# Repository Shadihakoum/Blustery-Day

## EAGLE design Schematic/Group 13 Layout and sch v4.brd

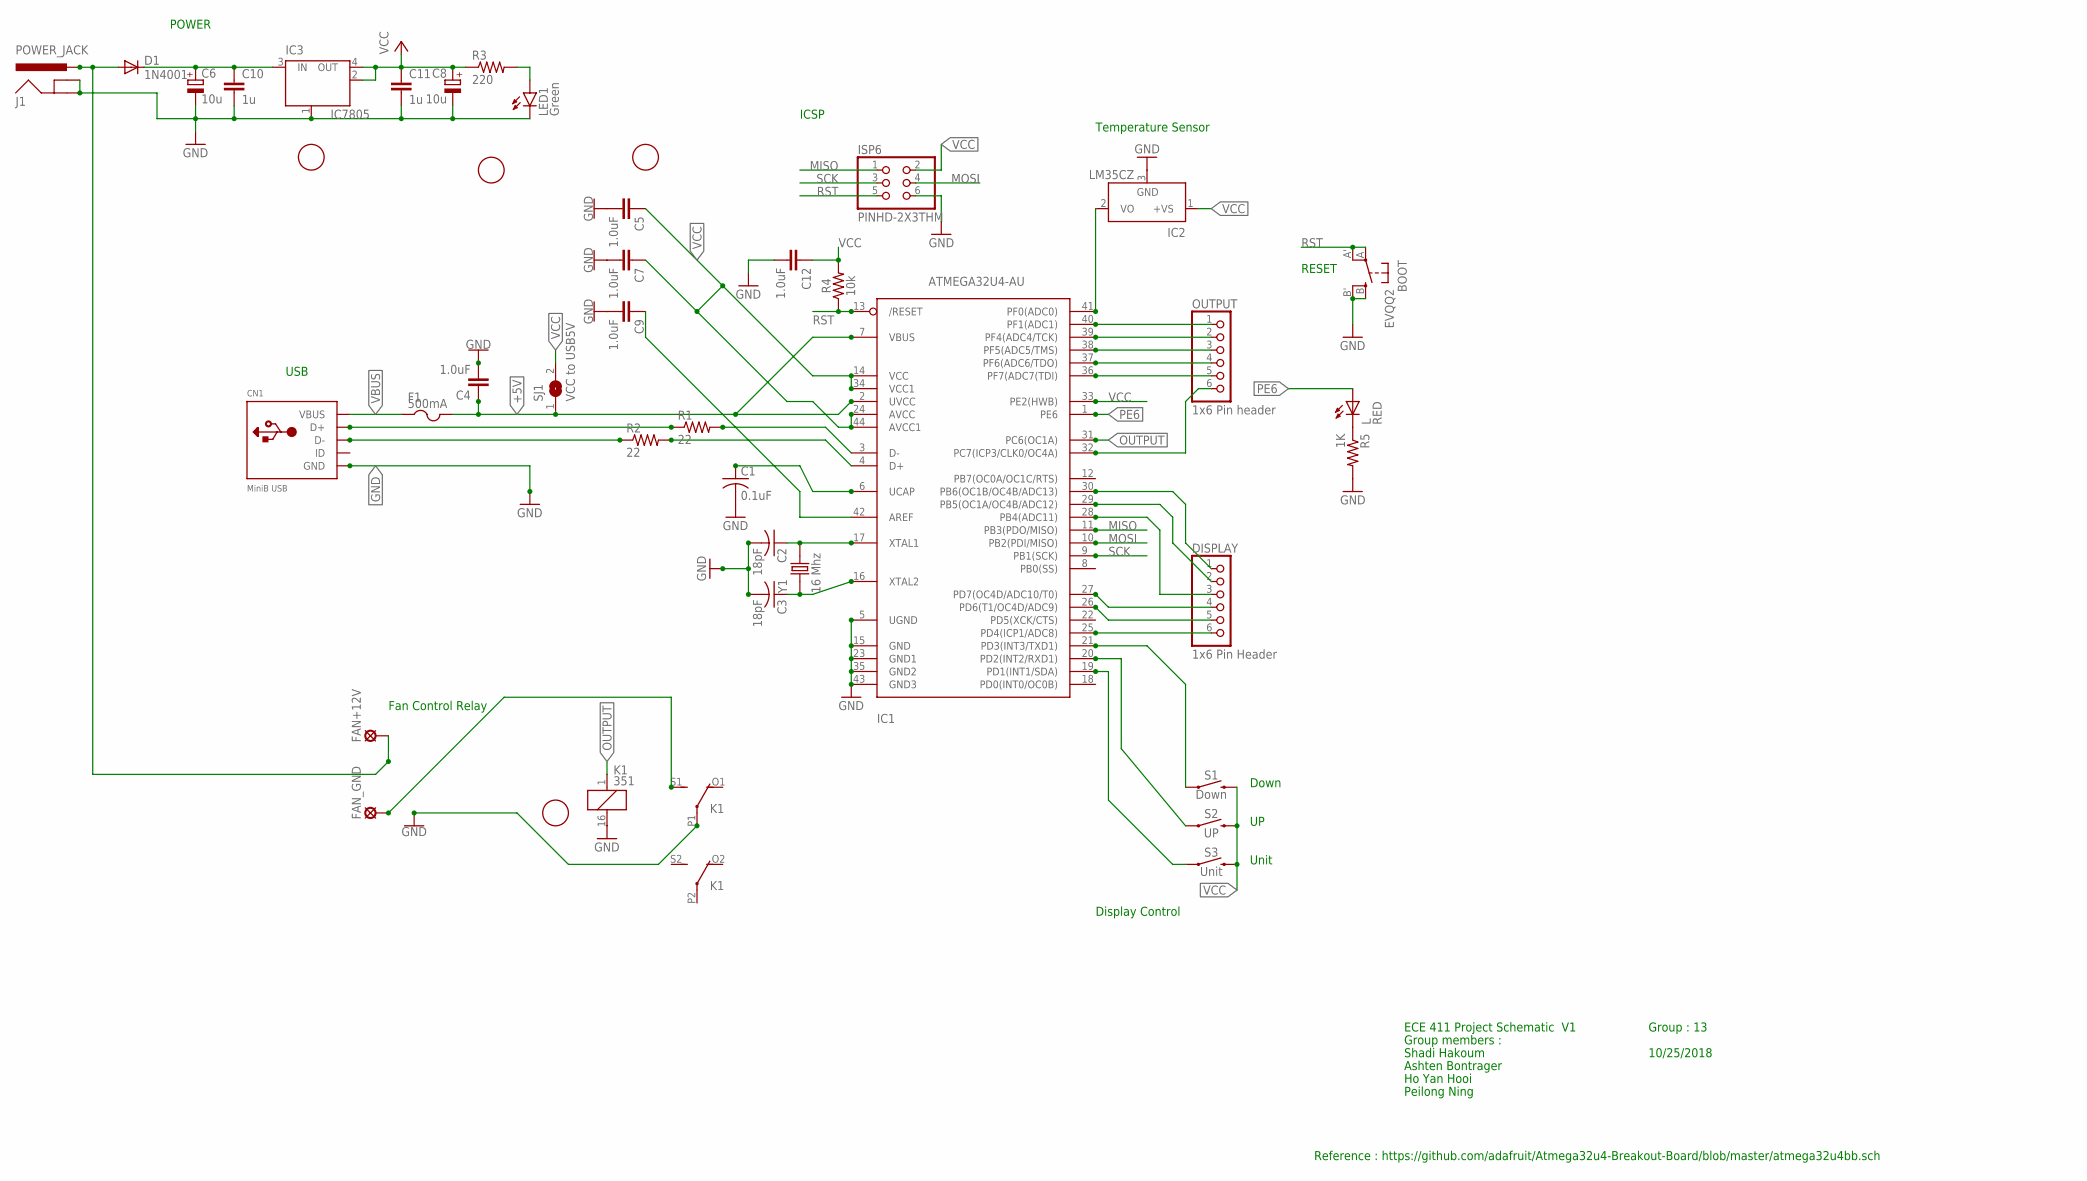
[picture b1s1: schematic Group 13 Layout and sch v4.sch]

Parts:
BOOT: EVQQ2; EVQ-Q2
C1: 0.1uF; C0805K
C2, C3: 18pF; C0805K
C4, C5, C7, C9, C12: 1.0uF; 0603
C6, C8: 10u; PANASONIC_C
C10, C11: 1u; C0805
CN1: MiniB USB; USB-MINIB
D1: 1N4001; DO220S
DISPLAY: 1x6 Pin Header; 1X06-BIG
F1: 500mA; R1206
FAN+12V: LSP10
FAN_GND: LSP11
IC1: ATMEGA32U4-AU; TQFP44
IC2: LM35CZ; TO92
IC3: IC7805; SOT223
ISP6: PINHD-2X3THM; ISP6
J1: POWER_JACK; POWER_JACK_PTH
K1: 351
L: RED; CHIPLED_0805
LED1: Green; LED5MM
OUTPUT: 1x6 Pin header; 1X06-BIG
R1, R2: 22; R0805
R3: 220; R0805
R4: 10k; AXIAL-0.3-KIT
R5: 1K; R0805
S1: Down; TACTILE_SWITCH_PTH_6.0MM
S2: UP; TACTILE_SWITCH_PTH_6.0MM
S3: Unit; TACTILE_SWITCH_PTH_6.0MM
SJ1: VCC to USB5V; SJ
U$1, U$2, U$3, U$6: FIDUCIAL; FIDUCIAL_1MM
Y1: 16 Mhz; XTAL_ECS-160-20-1X

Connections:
3.3V: C1.1, IC1.6 (UCAP)
+5V: C4.1, F1.2, IC1.2 (UVCC), IC1.7 (VBUS), SJ1.1
D+: CN1.D+, R1.1
D-: CN1.D-, R2.1
GND: BOOT.B (S), BOOT.B' (S1), C1.2, C2.2, C3.2, C4.2, C5.2, C6.-, C7.2, C8.-, C9.2, C10.2, C11.2, C12.2, CN1.GND, IC1.5 (UGND), IC1.15 (GND), IC1.23 (GND1), IC1.35 (GND2), IC1.43 (GND3), IC2.3 (GND), IC3.1 (GND/ADJ), ISP6.6, J1.GND, J1.GNDBREAK, K1.16 (2), K1.P1, LED1.K (C), R5.2
MISO: IC1.11 (PB3(PDO/MISO)), ISP6.1
MOSI: IC1.10 (PB2(PDI/MISO)), ISP6.4
unnamed: DISPLAY.6, IC1.25 (PD4(ICP1/ADC8))
unnamed: C6.+, C10.1, D1.C, IC3.3 (IN)
unnamed: IC1.3 (D-), R1.2
unnamed: IC1.4 (D+), R2.2
unnamed: LED1.A, R3.2
unnamed: IC1.40 (PF1(ADC1)), OUTPUT.1
unnamed: C2.1, IC1.17 (XTAL1), Y1.2
unnamed: C3.1, IC1.16 (XTAL2), Y1.1
unnamed: L.C, R5.1
unnamed: IC1.38 (PF5(ADC5/TMS)), OUTPUT.3
unnamed: DISPLAY.5, IC1.26 (PD6(T1/OC4D/ADC9))
unnamed: FAN_GND.MP, K1.S1 (S)
unnamed: DISPLAY.4, IC1.27 (PD7(OC4D/ADC10/T0))
unnamed: DISPLAY.3, IC1.28 (PB4(ADC11))
unnamed: DISPLAY.2, IC1.29 (PB5(OC1A/OC4B/ADC12))
unnamed: DISPLAY.1, IC1.30 (PB6(OC1B/OC4B/ADC13))
unnamed: IC1.19 (PD1(INT1/SDA)), S3.1
unnamed: IC1.20 (PD2(INT2/RXD1)), S2.1
unnamed: IC1.21 (PD3(INT3/TXD1)), S1.1
unnamed: IC1.37 (PF6(ADC6/TDO)), OUTPUT.4
unnamed: IC1.36 (PF7(ADC7(TDI)), OUTPUT.5
unnamed: IC1.32 (PC7(ICP3/CLK0/OC4A)), OUTPUT.6
unnamed: C9.1, IC1.42 (AREF)
unnamed: D1.A, FAN+12V.MP, J1.PWR
OUTPUT: IC1.31 (PC6(OC1A)), K1.1
PE6: IC1.1 (PE6), L.A
PF4: IC1.39 (PF4(ADC4/TCK)), OUTPUT.2
PF7: IC1.41 (PF0(ADC0)), IC2.2 (VO)
RST: BOOT.A, BOOT.A' (P1), IC1.13 (/RESET), ISP6.5, R4.P$1 (1)
SCK: IC1.9 (PB1(SCK)), ISP6.3
VBUS: CN1.VBUS, F1.1
VCC: C5.1, C7.1, C8.+, C11.1, C12.1, IC1.14 (VCC), IC1.24 (AVCC), IC1.33 (PE2(HWB)), IC1.34 (VCC1), IC1.44 (AVCC1), IC2.1 (+VS), IC3.2 (OUT), IC3.4 (OUT), ISP6.2, R3.1, R4.P$2 (2), S1.3 (2), S2.3 (2), S3.3 (2), SJ1.2

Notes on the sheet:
Temperature Sensor
ECE 411 Project Schematic V1
Reference : https://github.com/adafruit/Atmega32u4-Breakout-Board/blob/master/atmega32u4bb.sch
Group : 13
10/25/2018
Group members :
Shadi Hakoum
Ashten Bontrager
Ho Yan Hooi
Peilong Ning
Down
Display Control
RESET
ICSP
USB
Fan Control Relay
POWER
Unit

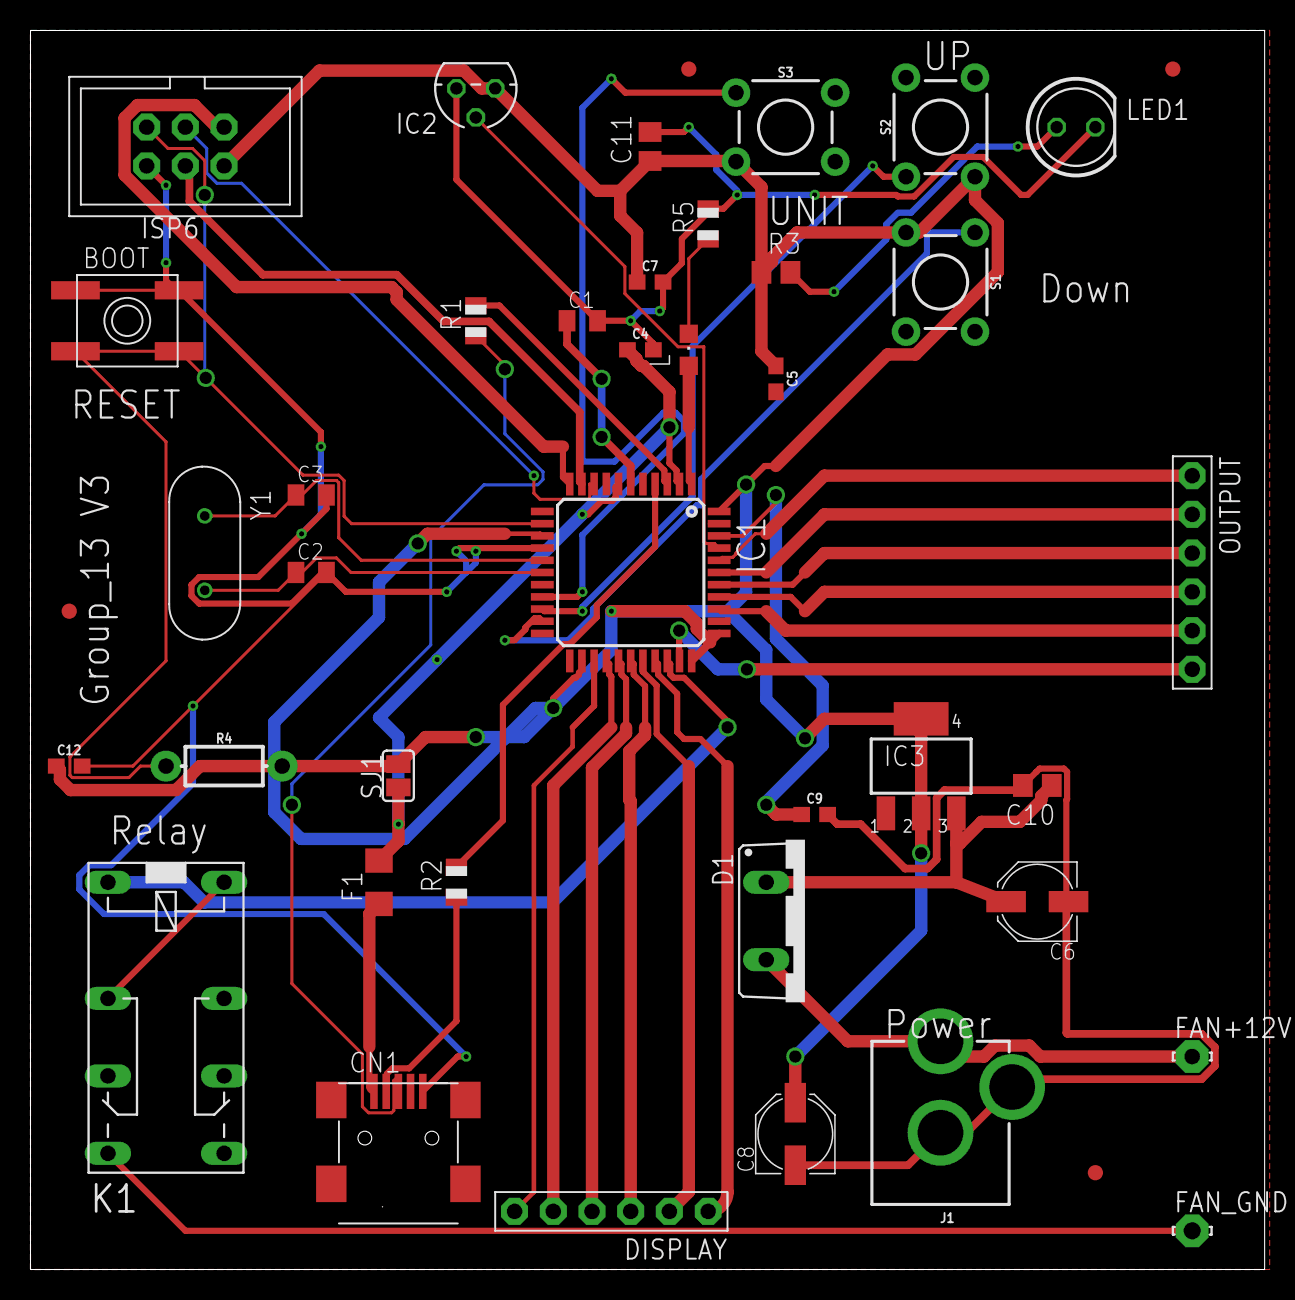
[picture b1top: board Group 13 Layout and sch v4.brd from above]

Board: 2 copper layers, 81.0 x 81.3 mm, 42 parts (0 on the bottom side), 39 nets.

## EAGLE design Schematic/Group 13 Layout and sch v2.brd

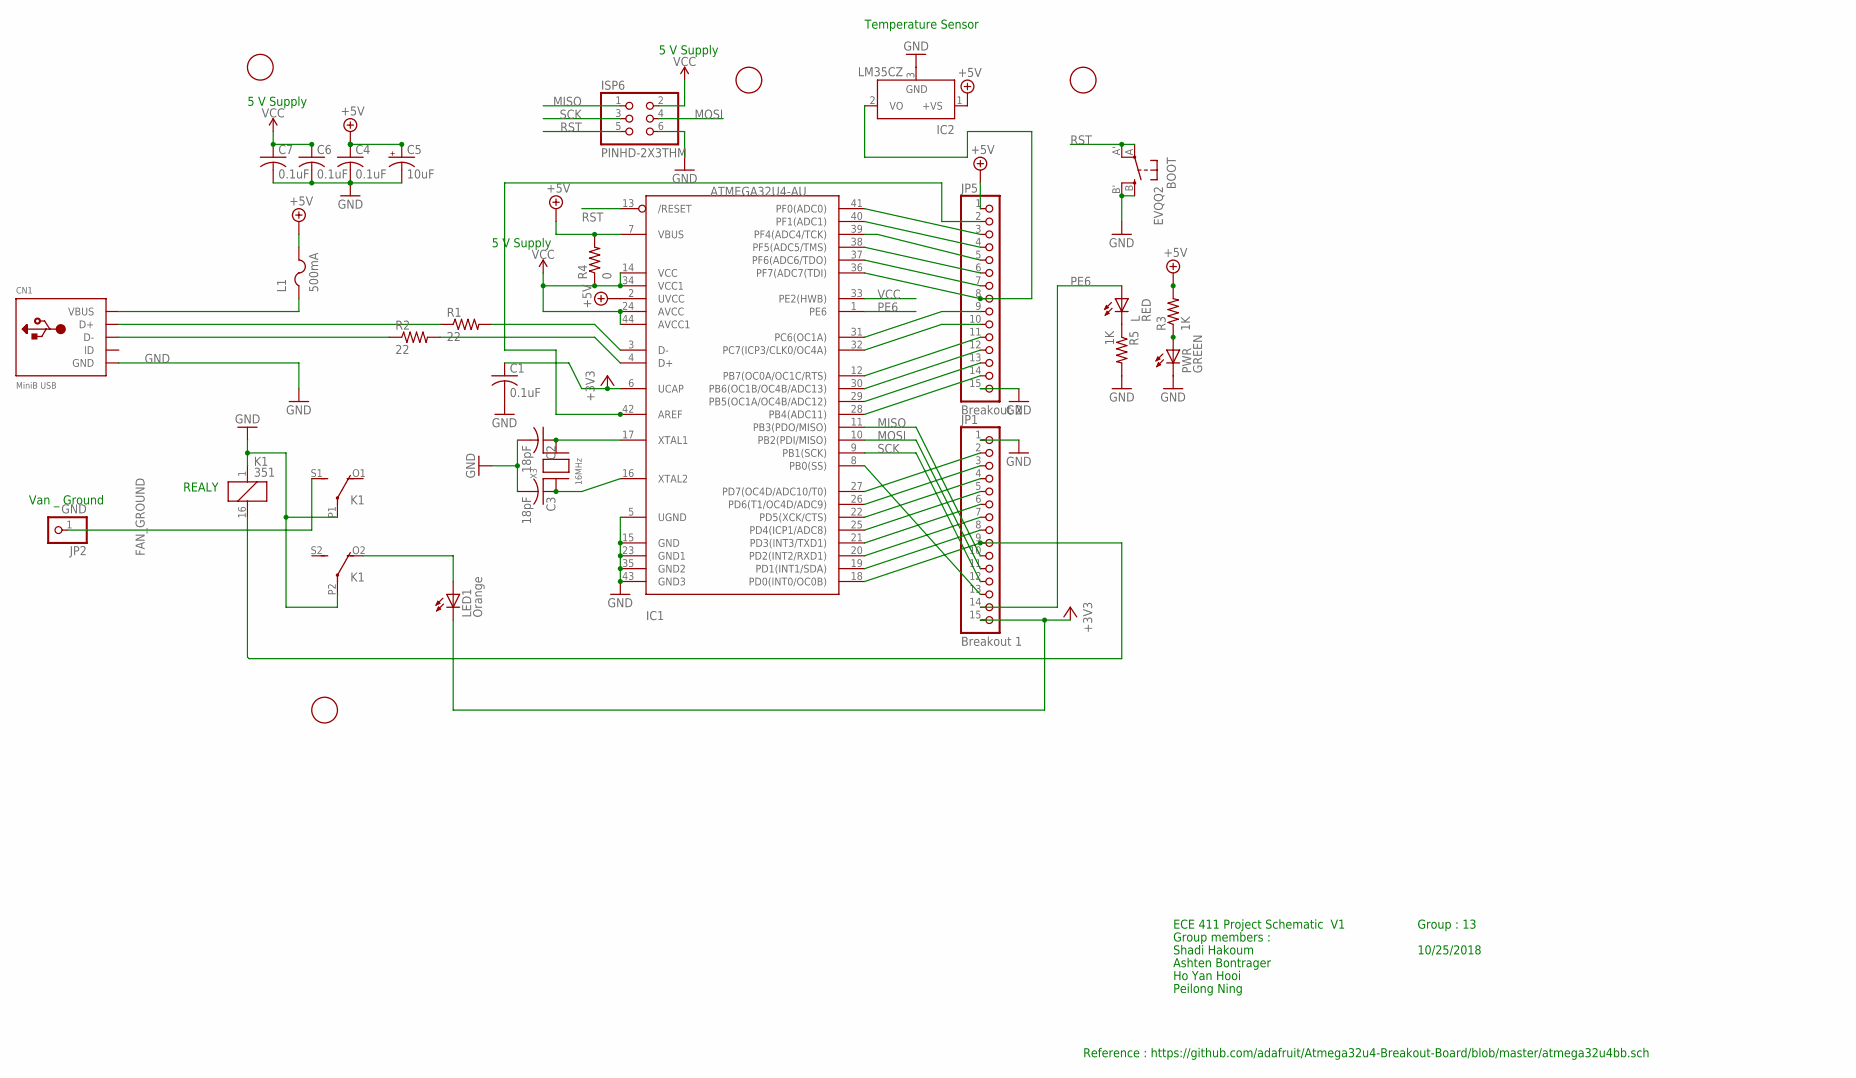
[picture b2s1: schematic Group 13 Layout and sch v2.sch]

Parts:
BOOT: EVQQ2; EVQ-Q2
C1, C4, C6, C7: 0.1uF; C0805K
C2, C3: 18pF; C0805K
C5: 10uF; A/3216-18R
CN1: MiniB USB; USB-MINIB
IC1: ATMEGA32U4-AU; TQFP44
IC2: LM35CZ; TO92
ISP6: PINHD-2X3THM; ISP6
JP1: Breakout 1; 1X15-CB
JP2: GND; 1X01
JP5: Breakout 2; 1X15-CB
K1: 351
L: RED; CHIPLED_0805
L1: 500mA; R1206
LED1: Orange; LED3MM
PWR: GREEN; CHIPLED_0805
R1, R2: 22; R0805
R3, R5: 1K; R0805
R4: 0; M1206
U$1, U$2, U$3, U$6: FIDUCIAL; FIDUCIAL_1MM
X3: 16MHz; NX5032

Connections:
+3V3: C1.1, IC1.6 (UCAP), JP1.15, LED1.K (C)
+5V: C4.1, C5.+, IC1.2 (UVCC), IC1.7 (VBUS), IC2.1 (+VS), JP5.1, L1.2, R3.2, R4.2
FAN_GROUND: JP2.1, K1.S1 (S)
GND: BOOT.B (S), BOOT.B' (S1), C1.2, C2.2, C3.2, C4.2, C5.-, C6.2, C7.2, CN1.GND, IC1.5 (UGND), IC1.15 (GND), IC1.23 (GND1), IC1.35 (GND2), IC1.43 (GND3), IC2.3 (GND), ISP6.6, JP1.1, JP5.15, K1.1, K1.P1, K1.P2, PWR.C, R5.2
MISO: IC1.11 (PB3(PDO/MISO)), ISP6.1, JP1.10
MOSI: IC1.10 (PB2(PDI/MISO)), ISP6.4, JP1.11
unnamed: PWR.A, R3.1
unnamed: CN1.D-, R2.1
unnamed: IC1.3 (D-), R1.2
unnamed: IC1.4 (D+), R2.2
unnamed: CN1.D+, R1.1
unnamed: IC1.42 (AREF), JP5.2
unnamed: IC1.37 (PF6(ADC6/TDO)), JP5.7
unnamed: C2.1, IC1.17 (XTAL1), X3.P$2
unnamed: C3.1, IC1.16 (XTAL2), X3.P$1
unnamed: L.C, R5.1
unnamed: K1.O2 (O), LED1.A
unnamed: IC1.31 (PC6(OC1A)), JP5.9
unnamed: IC1.32 (PC7(ICP3/CLK0/OC4A)), JP5.10
PB0: IC1.8 (PB0(SS)), JP1.13
PB4: IC1.28 (PB4(ADC11)), JP5.14
PB5: IC1.29 (PB5(OC1A/OC4B/ADC12)), JP5.13
PB6: IC1.30 (PB6(OC1B/OC4B/ADC13)), JP5.12
PB7: IC1.12 (PB7(OC0A/OC1C/RTS)), JP5.11
PD0: IC1.18 (PD0(INT0/OC0B)), JP1.9, K1.16 (2)
PD1: IC1.19 (PD1(INT1/SDA)), JP1.8
PD2: IC1.20 (PD2(INT2/RXD1)), JP1.7
PD3: IC1.21 (PD3(INT3/TXD1)), JP1.6
PD4: IC1.25 (PD4(ICP1/ADC8)), JP1.5
PD5: IC1.22 (PD5(XCK/CTS)), JP1.4
PD6: IC1.26 (PD6(T1/OC4D/ADC9)), JP1.3
PD7: IC1.27 (PD7(OC4D/ADC10/T0)), JP1.2
PE6: IC1.1 (PE6), JP1.14, L.A
PF0: IC1.41 (PF0(ADC0)), JP5.3
PF1: IC1.40 (PF1(ADC1)), JP5.4
PF4: IC1.39 (PF4(ADC4/TCK)), JP5.5
PF5: IC1.38 (PF5(ADC5/TMS)), JP5.6
PF7: IC1.36 (PF7(ADC7(TDI)), IC2.2 (VO), JP5.8
RST: BOOT.A, BOOT.A' (P1), IC1.13 (/RESET), ISP6.5
SCK: IC1.9 (PB1(SCK)), ISP6.3, JP1.12
VBUS: CN1.VBUS, L1.1
VCC: C6.1, C7.1, IC1.14 (VCC), IC1.24 (AVCC), IC1.33 (PE2(HWB)), IC1.34 (VCC1), IC1.44 (AVCC1), ISP6.2, R4.1

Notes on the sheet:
REALY
5 V Supply
Temperature Sensor
Van _ Ground
ECE 411 Project Schematic V1
Reference : https://github.com/adafruit/Atmega32u4-Breakout-Board/blob/master/atmega32u4bb.sch
Group : 13
10/25/2018
Group members :
Shadi Hakoum
Ashten Bontrager
Ho Yan Hooi
Peilong Ning

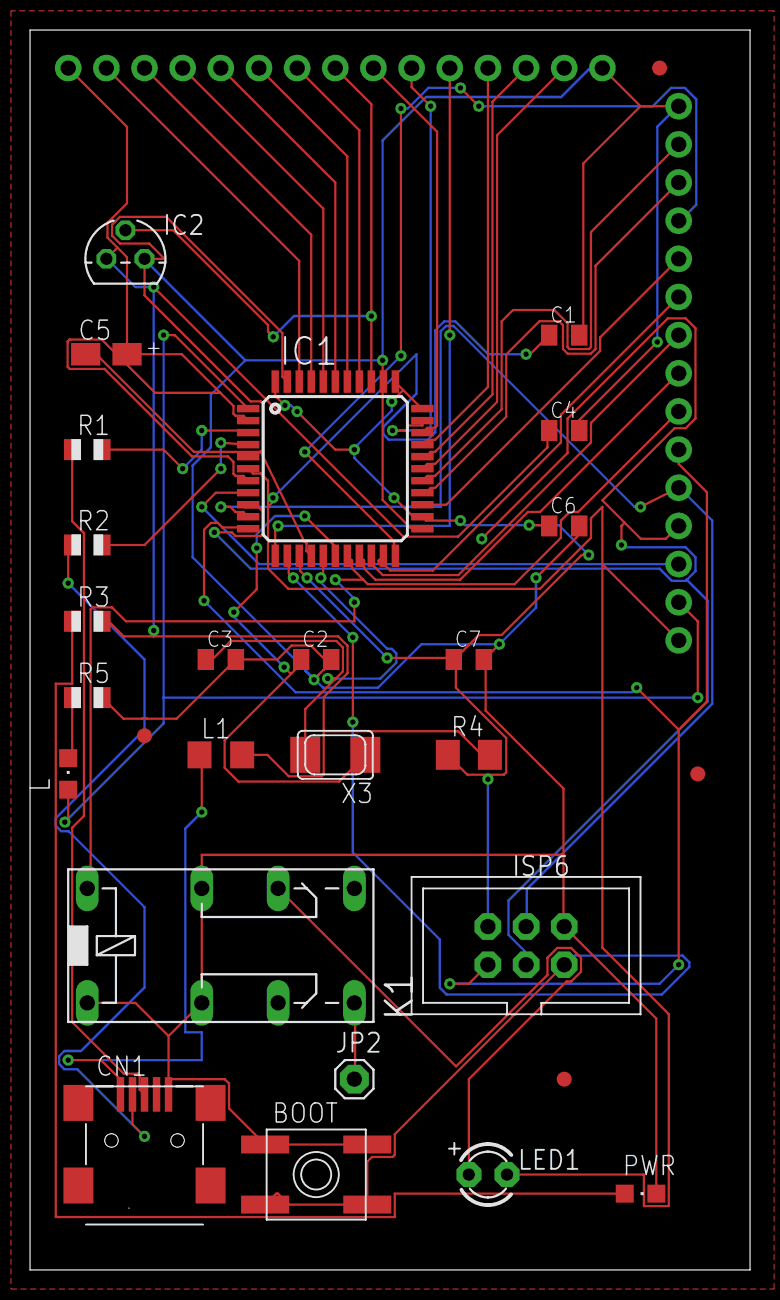
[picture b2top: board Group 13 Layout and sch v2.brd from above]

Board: 2 copper layers, 47.9 x 82.5 mm, 30 parts (0 on the bottom side), 42 nets.

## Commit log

2018-10-06 Create Updates
2018-10-06 Update Updates
2018-10-25 Preliminary schematic before LCD display and user input devices added. Generated in EagleCad
2018-10-25 Photo of preliminary schematic, doesn't include LCD display
2018-10-27 Preliminary code for project, needs a lot of work.
2018-10-27 Product Design Specification. Please review, make any comments/changes and we will submit to D2L
2018-10-27 Product Design Specification. Shadi-Please review, make any comments/changes and submit to D2L.
2018-10-30 Current code idea, incomplete and needs testing
2018-10-31 Complete code for controlling fan, LCD, and buttons.
2018-10-31 Removed extra spaces at end of code
2018-11-01 Updated the serial port from 9600 to 19200, Arduino indicated that the new boot loaders have the serial ports operating at this speed.
2018-11-01 Fixed missing semicolons
2018-11-01 First sketch with successful compile
2018-11-03 Add files via upload
    Brd file with auto trace for reference
2018-11-07 Added fan control statements.
2018-11-09 Modified bootloader supplied by Jeremy from https://www.eevblog.com/forum/microcontrollers/atmegaa32u4-usb-with-internal-rc-clock/
    Changed the pin I/O numbers to reflect the arduino standard
2018-11-13 Removed delays, because pause in between button press and system response was to long
2018-11-16 Updated lines controlling button behavior, added delay for stability(when handling button press), added then removed lines for testing button behavior(can re-add later)
2018-11-27 Updated code. All buttons currently working and LCD displays correct values

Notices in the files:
parts and their libraries:
SparkFun-PowerSymbols: Licensing: Creative Commons ShareAlike 4.0 International - https://creativecommons.org/licenses/by-sa/4.0
